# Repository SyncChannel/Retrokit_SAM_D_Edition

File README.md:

# Retrokit SAM D Edition
A 2016 Redesign of the classic Retrokit using the Atmel SAM D09<br><br>
<http://syncchannel.blogspot.com/2016/07/atmel-retrokit-sam-d-edition.html>

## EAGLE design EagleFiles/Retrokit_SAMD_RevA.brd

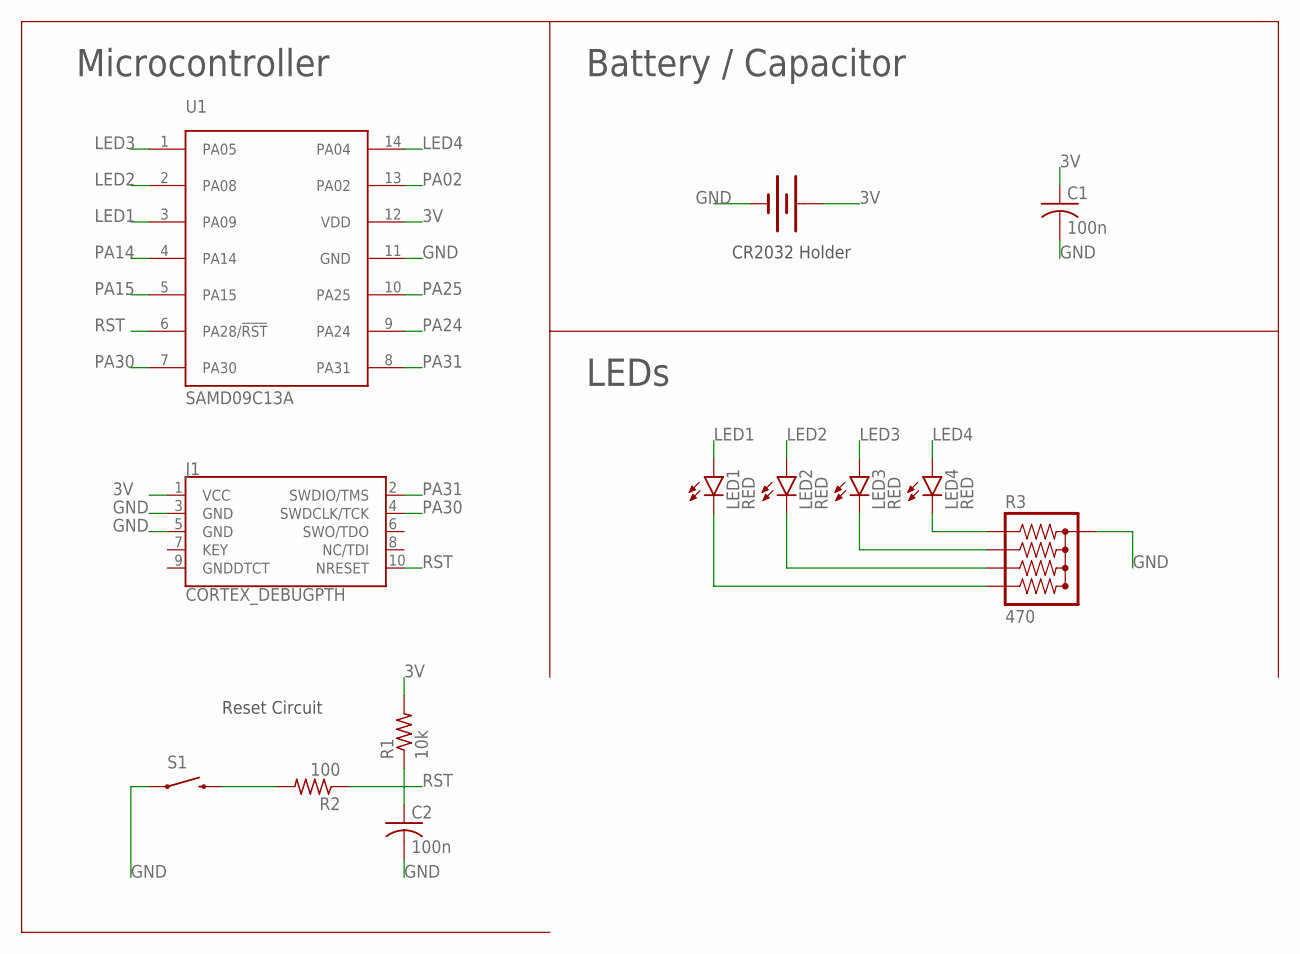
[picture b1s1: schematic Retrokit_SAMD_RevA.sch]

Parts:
BAT1: BATTERYFOB; BATTERY_20MM_PTH_COMPACT
C1: 100n; C025-024X044
C2: 100n; C0805
J1: CORTEX_DEBUGPTH; 2X5-PTH-1.27MM
LED1, LED2, LED3, LED4: RED; LED3MM
R1: 10k; R0805
R2: 100; R0805
R3: 470; RBUSSED-5SIP
S1: SWITCH-MOMENTARY-2PTH; TACTILE-PTH
U1: SAMD09C13A; SO14-NARROWPADS

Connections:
3V: BAT1.1 (+), C1.1, J1.1 (VCC), R1.2, U1.12 (VDD)
GND: BAT1.2 (-), C1.2, C2.2, J1.3 (GND), J1.5 (GND), R3.GND, S1.1, U1.11 (GND)
LED1: LED1.A, U1.3 (PA09)
LED2: LED2.A, U1.2 (PA08)
LED3: LED3.A, U1.1 (PA05)
LED4: LED4.A, U1.14 (PA04)
unnamed: R2.2, S1.3 (2)
unnamed: LED1.K (C), R3.R4
unnamed: LED2.K (C), R3.R3
unnamed: LED3.K (C), R3.R2
unnamed: LED4.K (C), R3.R1
PA02: U1.13 (PA02)
PA14: U1.4 (PA14)
PA15: U1.5 (PA15)
PA24: U1.9 (PA24)
PA25: U1.10 (PA25)
PA30: J1.4 (SWDCLK/TCK), U1.7 (PA30)
PA31: J1.2 (SWDIO/TMS), U1.8 (PA31)
RST: C2.1, J1.10 (NRESET), R1.1, R2.1, U1.6 (PA28/!RST)

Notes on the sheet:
Microcontroller
Reset Circuit
CR2032 Holder
Battery / Capacitor
LEDs

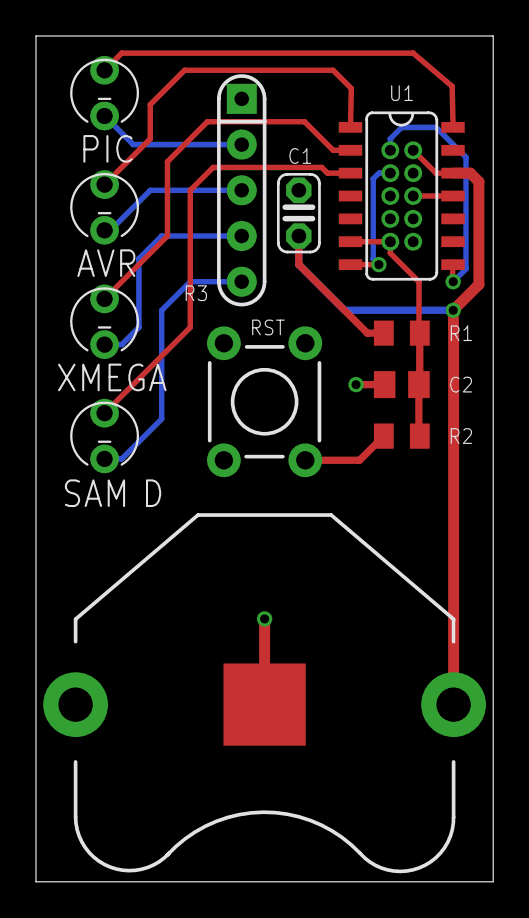
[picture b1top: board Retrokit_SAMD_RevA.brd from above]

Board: 2 copper layers, 25.4 x 47.0 mm, 13 parts (1 on the bottom side), 14 nets.

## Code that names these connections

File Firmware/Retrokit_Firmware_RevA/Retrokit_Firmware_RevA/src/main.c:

/*
 * Retrokit_Firmware_RevA
 * Device: SAMD09C13A
 *
 * Created: 7/11/2016
 * Author : Dan Watson
 *			syncchannel.blogspot.com
 */

/* Calculations for demonstration LED blinks:
 *	- The four devices I have in mind for this demonstration:
 *		SAM D09, 48MHz, 48 DMIPS
 *		ATxmega256A3BU, 32MHz, 32 MIPS
 *		ATmega328P, 20MHz, 20 MIPS
 *		PIC 16F627A, 20MHz, 5 MIPS
 *
 *	- Blink rate and completion time are based on MIPS/DMIPS.
 *
 *	- Want blinks to take 10 seconds (10,000 milliseconds) in total. The slowest device is the PIC (5 MIPS).
 *	  The SysTick timer will interrupt every 1ms (1MHz clock / 1000).
 *	  So let's set the counter = 10000.
 *	  Every 1ms, the SAM D09 would increment the counter 48, the XMEGA increments 32, etc.
 *	  But we will increment a single counter and pre-computer the target completion values.
 *	  
 *	  SAM D: 1/10th complete = 111, complete at counter value = 1,110
 *	  XMEGA: 1/10th complete = 156, complete at counter value = 1,560
 *	    AVR: 1/10th complete = 250, complete at counter value = 2,500
 *	    PIC: 1/10th complete = 1000, complete at counter value = 10,000
*/

#include "samd09.h"
#include "clock.h"
#include "port.h"
#include "power.h"

#define SAMDLED PIN_PA09
#define XMEGALED PIN_PA08
#define AVRLED PIN_PA05
#define PICLED PIN_PA04

volatile uint16_t counter = 0;

void SysTick_Handler(void)
{
	counter++;
	
	// Check for updates on each of the four LEDs
	
	if (counter % 111 == 0)
		port_pin_set_output_level(SAMDLED,true);
    else if (counter % 131 == 0 && counter < 1110)
		port_pin_set_output_level(SAMDLED,false);
		
	if (counter % 156 == 0)
		port_pin_set_output_level(XMEGALED,true);
	else if (counter % 176 == 0 && counter < 1560)
		port_pin_set_output_level(XMEGALED,false);
		
	if (counter % 250 == 0)
		port_pin_set_output_level(AVRLED,true);
	else if (counter % 270 == 0 && counter < 2500)
		port_pin_set_output_level(AVRLED,false);
		
	if (counter % 1000 == 0)
		port_pin_set_output_level(PICLED,true);
	else if (counter % 1020 == 0 && counter < 10000)
		port_pin_set_output_level(PICLED,false);
		
	// Go to sleep after 5 seconds of all LEDs on
	if (counter == 15000)
	{
		port_group_set_output_level(&PORTA,0xFFFFFFFF,0);
		port_group_set_config(&PORTA,0xFFFFFFFF,0);
		system_sleep();
	}
}

// Configure the SysTick timer to interrupt every 1ms
static void configure_systick_handler(void)
{
	SysTick->CTRL = 0;
	SysTick->LOAD = 1000;
	SysTick->VAL = 0;
	SysTick->CTRL = SysTick_CTRL_CLKSOURCE_Msk | SysTick_CTRL_TICKINT_Msk | SysTick_CTRL_ENABLE_Msk;
}

int main(void)
{
	SystemInit();
	system_clock_init(); // Internal RC, DIV8 (1MHz)
	configure_systick_handler(); // Interrupt every 1ms
	system_set_sleepmode(SYSTEM_SLEEPMODE_STANDBY); // Deep sleep mode
	
	
	// Configure output pins for LEDs
	struct port_config pin_conf_out;
	port_get_config_defaults(&pin_conf_out);
	pin_conf_out.direction = PORT_PIN_DIR_OUTPUT;
	port_pin_set_config(SAMDLED, &pin_conf_out);
	port_pin_set_config(XMEGALED, &pin_conf_out);
	port_pin_set_config(AVRLED, &pin_conf_out);
	port_pin_set_config(PICLED, &pin_conf_out);
	
	while (1)
	{
		// Do nothing. Everything is handled in the SysTick timer interrupt.
	}
}

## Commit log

2016-07-14 :lollipop: Added .gitattributes & .gitignore files
2016-07-14 Added Eagle Files and Firmware
2016-07-14 Create License file
2016-07-14 Updated firmware files
2016-07-14 Updated readme with blog post URL

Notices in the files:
parts and their libraries:
SparkFun-ConnectorsNEW: Licensing: Creative Commons ShareAlike 4.0 International - https://creativecommons.org/licenses/by-sa/4.0
